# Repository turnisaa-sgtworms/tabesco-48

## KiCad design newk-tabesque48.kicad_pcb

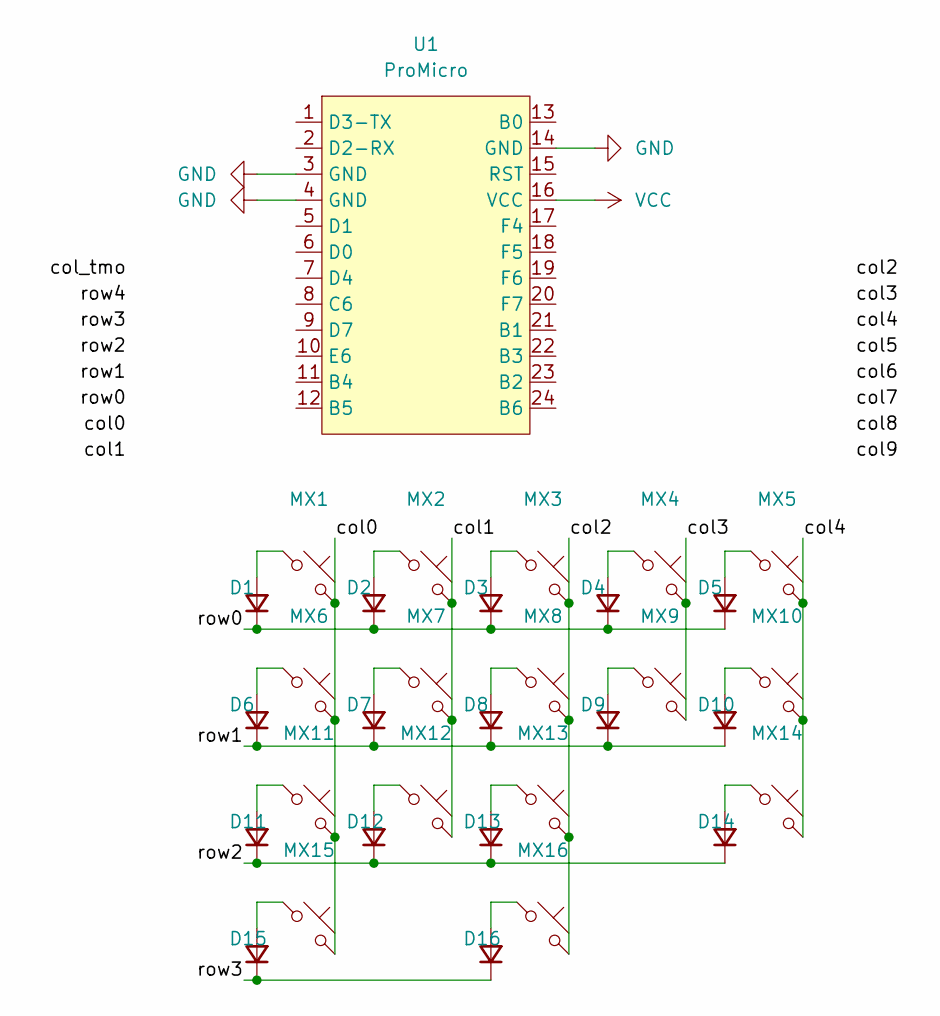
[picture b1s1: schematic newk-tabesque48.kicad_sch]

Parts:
D1, D2, D3, D4, D5, D6, D7, D8, D9, D10, D11, D12, D13, D14, D15, D16: D_Small; D_SOD-123
MX1, MX2, MX3, MX4, MX5, MX6, MX7, MX8, MX9, MX10, MX11, MX12, MX13, MX14, MX15, MX16: MX_SW_HS; SW_MX_HS_CPG151101S11_1u
U1: ProMicro; ProMicro_USBdn

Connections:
/col0: MX1.2, MX6.2, MX11.2, MX15.2
/col1: MX2.2, MX7.2, MX12.2
/col2: MX3.2, MX8.2, MX13.2, MX16.2
/col3: MX4.2, MX9.2
/col4: MX5.2, MX10.2, MX14.2
/row0: D1.1 (K), D2.1 (K), D3.1 (K), D4.1 (K), D5.1 (K)
/row1: D6.1 (K), D7.1 (K), D8.1 (K), D9.1 (K), D10.1 (K)
/row2: D11.1 (K), D12.1 (K), D13.1 (K), D14.1 (K)
/row3: D15.1 (K), D16.1 (K)
GND: U1.3 (GND), U1.4 (GND), U1.14 (GND)
unnamed: D1.2 (A), MX1.1
unnamed: D2.2 (A), MX2.1
unnamed: D3.2 (A), MX3.1
unnamed: D4.2 (A), MX4.1
unnamed: D5.2 (A), MX5.1
unnamed: D6.2 (A), MX6.1
unnamed: D7.2 (A), MX7.1
unnamed: D8.2 (A), MX8.1
unnamed: D9.2 (A), MX9.1
unnamed: D10.2 (A), MX10.1
unnamed: D11.2 (A), MX11.1
unnamed: D12.2 (A), MX12.1
unnamed: D13.2 (A), MX13.1
unnamed: D14.2 (A), MX14.1
unnamed: D15.2 (A), MX15.1
unnamed: D16.2 (A), MX16.1
VCC: U1.16 (VCC)

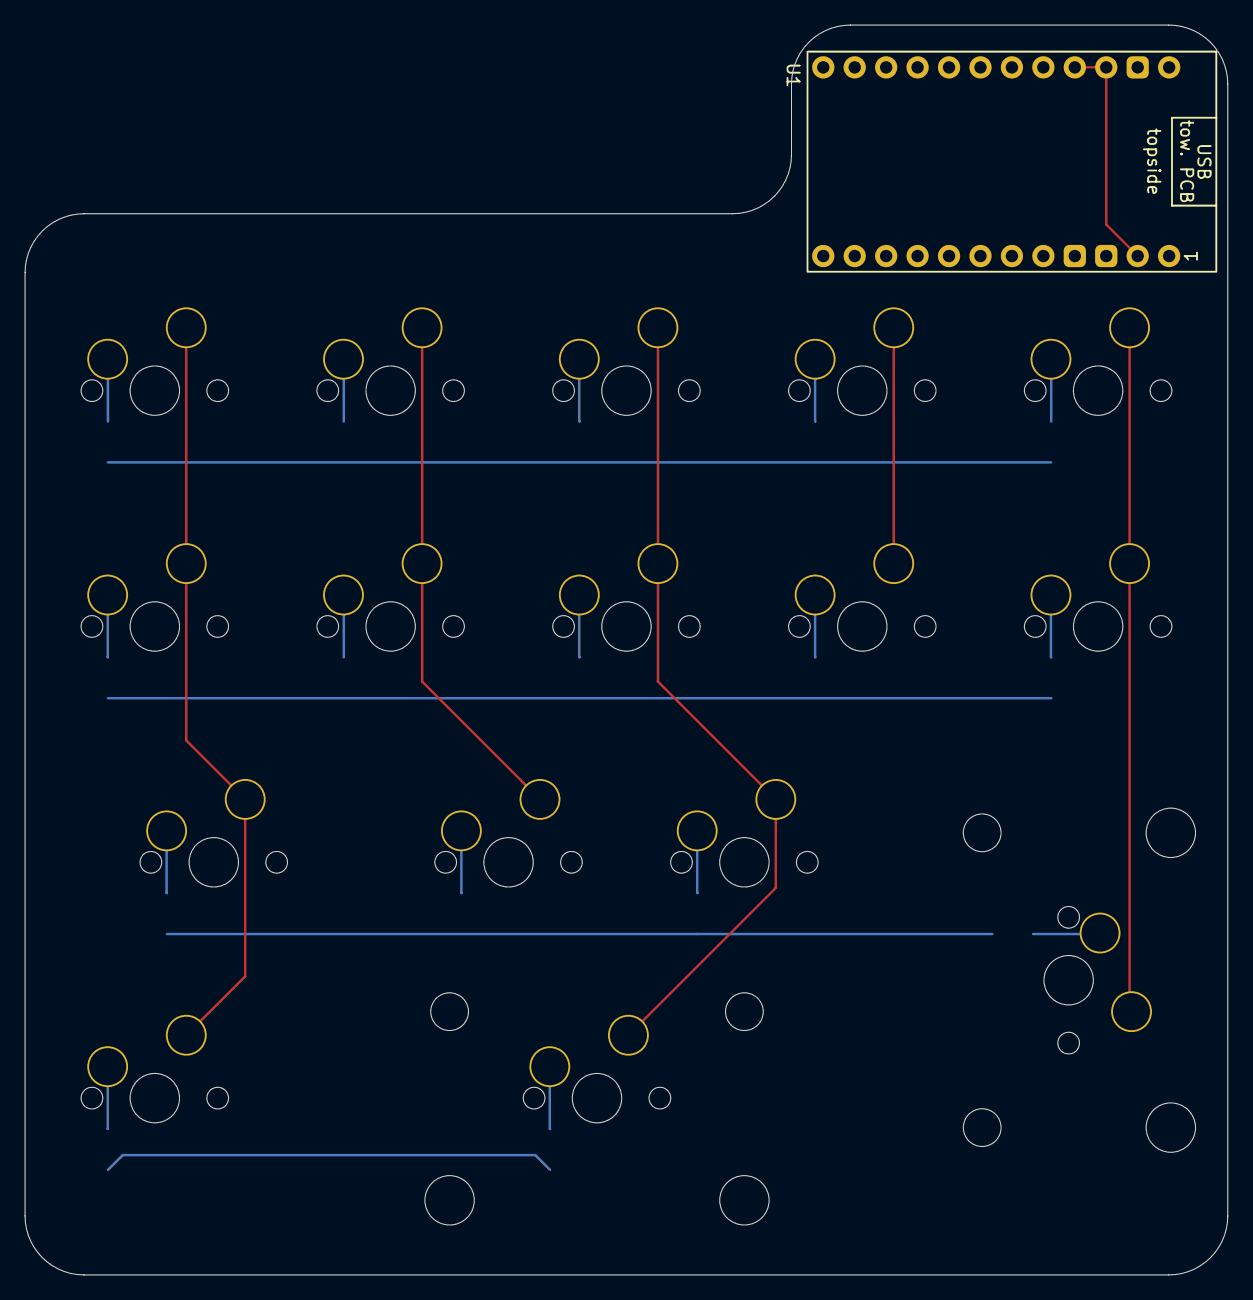
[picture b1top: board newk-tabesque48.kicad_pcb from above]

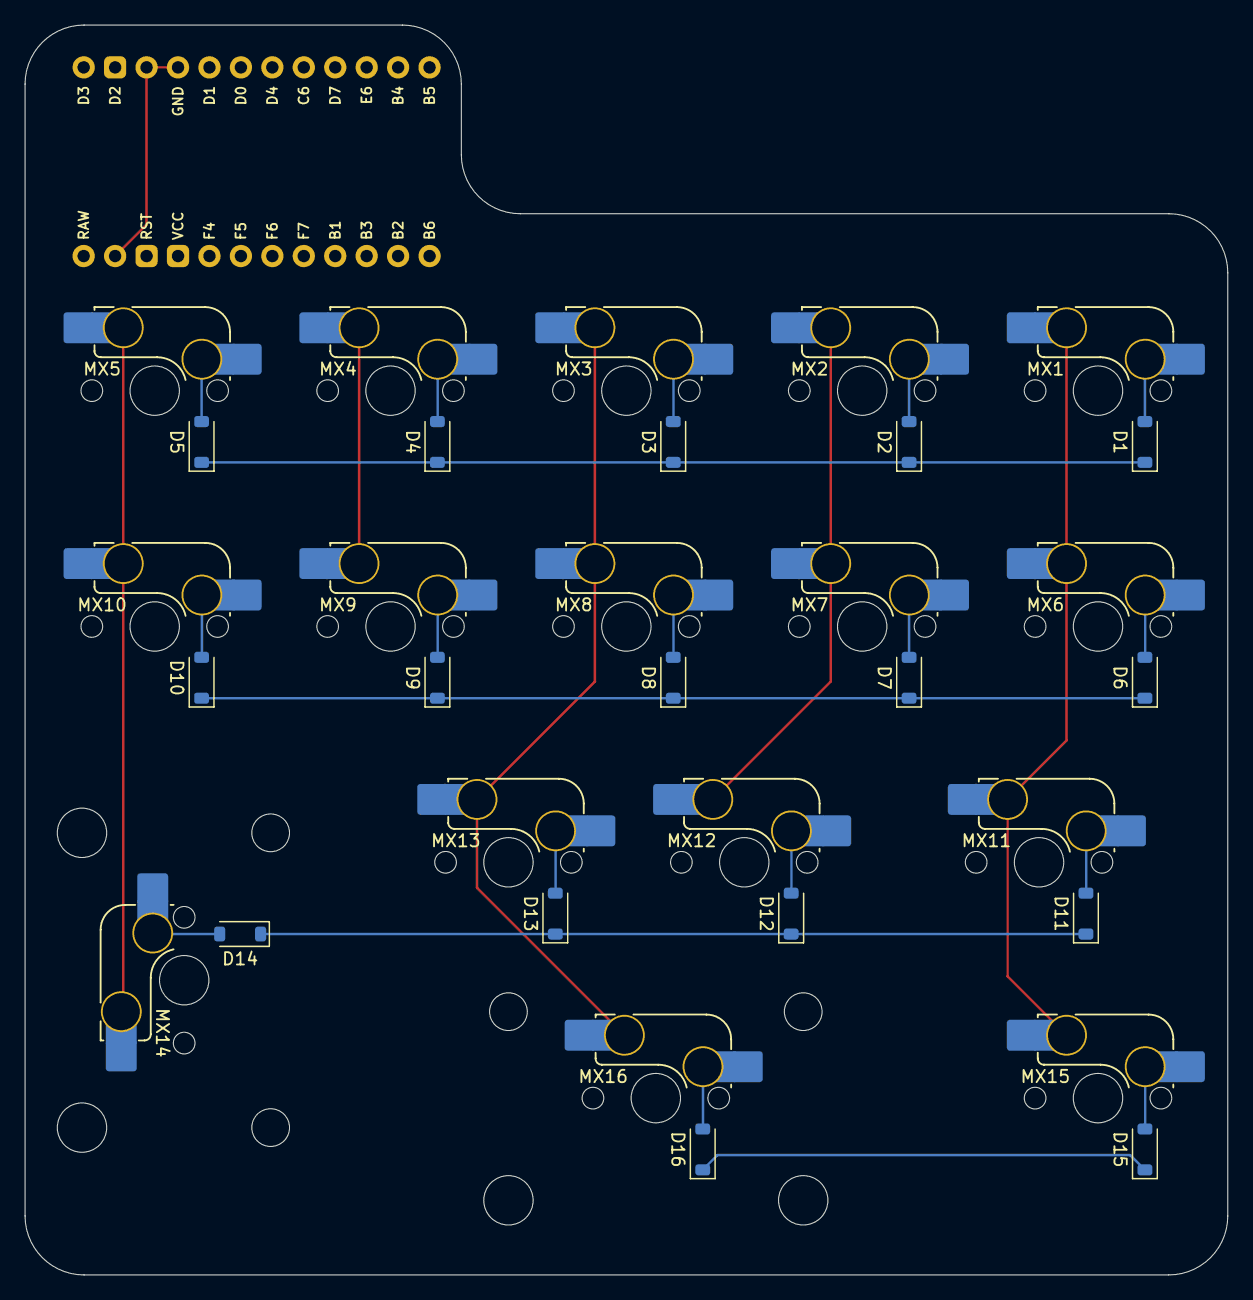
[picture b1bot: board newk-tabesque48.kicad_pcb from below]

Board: 2 copper layers, 97.2 x 101.0 mm, 33 parts (32 on the bottom side), 26 nets.

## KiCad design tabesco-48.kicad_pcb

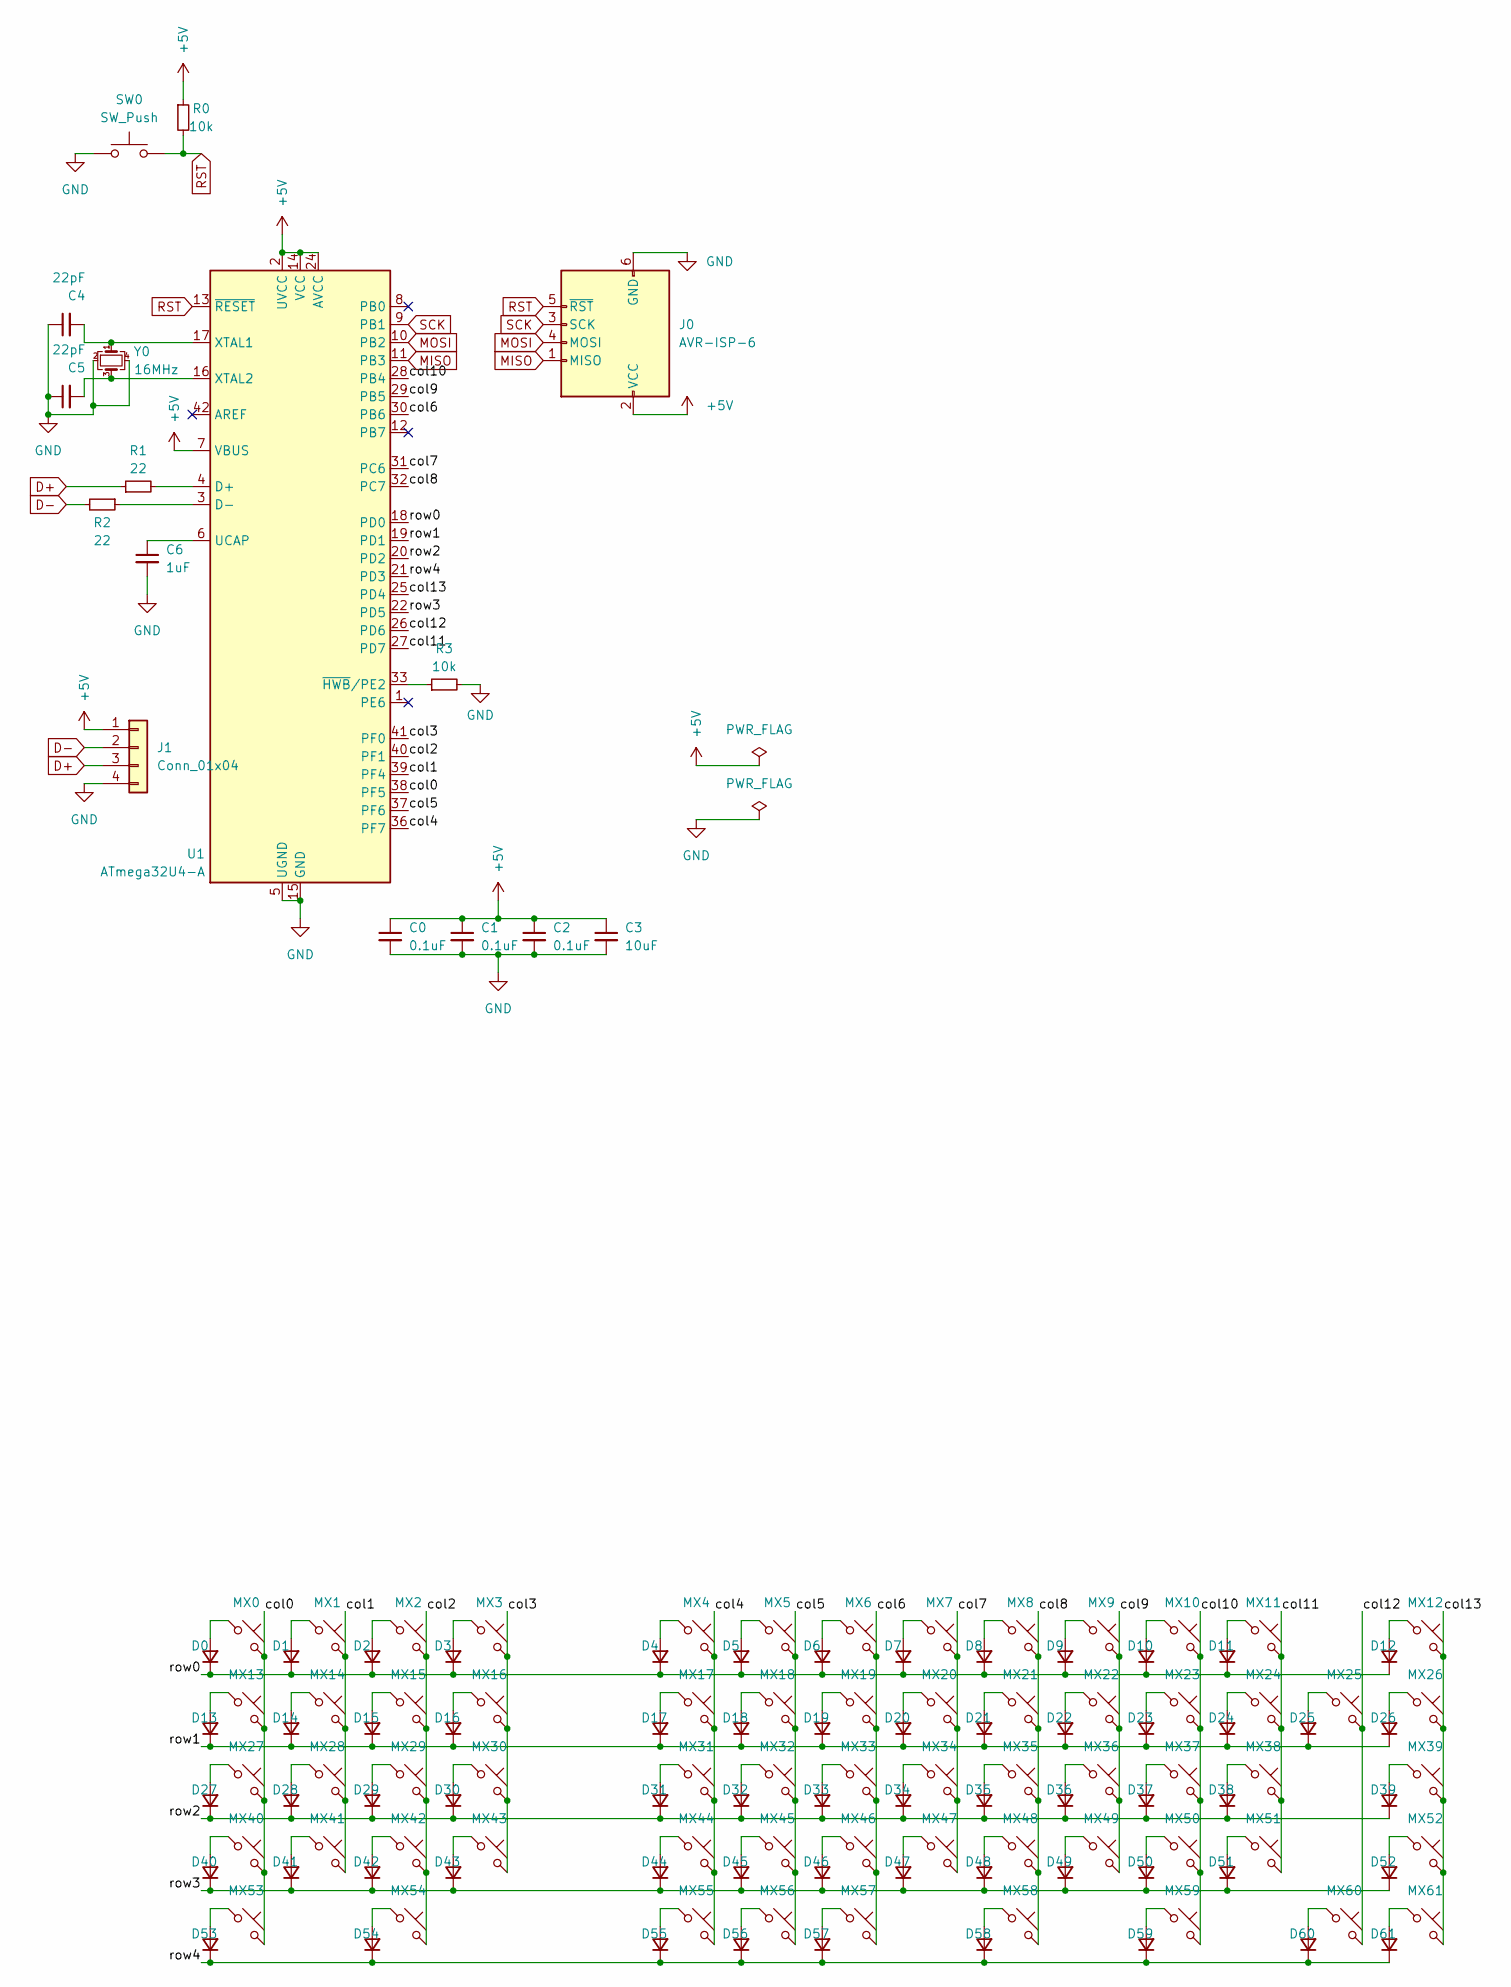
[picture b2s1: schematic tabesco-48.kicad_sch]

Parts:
C0, C1, C2: 0.1uF; C_0805_2012Metric
C3: 10uF; C_0805_2012Metric
C4, C5: 22pF; C_0805_2012Metric
C6: 1uF; C_0805_2012Metric
D0, D1, D2, D3, D4, D5, D6, D7, D8, D9, D10, D11, D12, D13, D14, D15, D16, D17, D18, D19, D20, D21, D22, D23, D24, D25, D26, D27, D28, D29, D30, D31, D32, D33, D34, D35, D36, D37, D38, D39, D40, D41, D42, D43, D44, D45, D46, D47, D48, D49, D50, D51, D52, D53, D54, D55, D56, D57, D58, D59, D60, D61: D_Small; D_SOD-123
J0: AVR-ISP-6; PinHeader_2x03_P1.00mm_Vertical
J1: Conn_01x04; JST_SH_SM04B-SRSS-TB_1x04-1MP_P1.00mm_Horizontal
MX0, MX1, MX2, MX3, MX5, MX6, MX7, MX8, MX9, MX10, MX11, MX13, MX14, MX15, MX16, MX18, MX19, MX20, MX21, MX22, MX23, MX24, MX25, MX27, MX28, MX29, MX30, MX32, MX33, MX34, MX35, MX36, MX37, MX38, MX40, MX41, MX42, MX43, MX45, MX46, MX47, MX48, MX49, MX50, MX51, MX52, MX53, MX54, MX56, MX58, MX59, MX60, MX61: MX_SW_HS; SW_MX_HS_CPG151101S11_1u
MX4, MX12, MX31, MX39: MX_SW_HS; SW_MX_HS_CPG151101S11_1.75u
MX17, MX26, MX55, MX57: MX_SW_HS; SW_MX_HS_CPG151101S11_1.25u
MX44: MX_SW_HS; SW_MX_HS_CPG151101S11_1.5u
R0, R3: 10k; R_0805_2012Metric
R1, R2: 22; R_0805_2012Metric
SW0: SW_Push; SW_Tactile_Straight_KSA0Axx1LFTR
U1: ATmega32U4-A; TQFP-44_10x10mm_P0.8mm
Y0: 16MHz; Crystal_SMD_3225-4Pin_3.2x2.5mm

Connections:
+5V: C0.1, C1.1, C2.1, C3.1, J0.2 (VCC), J1.1, R0.1, U1.2 (UVCC), U1.7 (VBUS), U1.14 (VCC), U1.24 (AVCC), U1.34 (VCC), U1.44 (AVCC)
/col0: MX0.2, MX13.2, MX27.2, MX40.2, MX53.2, U1.38 (PF5)
/col1: MX1.2, MX14.2, MX28.2, MX41.2, U1.39 (PF4)
/col2: MX2.2, MX15.2, MX29.2, MX42.2, MX54.2, U1.40 (PF1)
/col3: MX3.2, MX16.2, MX30.2, MX43.2, U1.41 (PF0)
/col4: MX4.2, MX17.2, MX31.2, MX44.2, MX55.2, U1.36 (PF7)
/col5: MX5.2, MX18.2, MX32.2, MX45.2, MX56.2, U1.37 (PF6)
/col6: MX6.2, MX19.2, MX33.2, MX46.2, MX57.2, U1.30 (PB6)
/col7: MX7.2, MX20.2, MX34.2, MX47.2, U1.31 (PC6)
/col8: MX8.2, MX21.2, MX35.2, MX48.2, MX58.2, U1.32 (PC7)
/col9: MX9.2, MX22.2, MX36.2, MX49.2, U1.29 (PB5)
/col10: MX10.2, MX23.2, MX37.2, MX50.2, MX59.2, U1.28 (PB4)
/col11: MX11.2, MX24.2, MX38.2, MX51.2, U1.27 (PD7)
/col12: MX25.2, MX60.2, U1.26 (PD6)
/col13: MX12.2, MX26.2, MX39.2, MX52.2, MX61.2, U1.25 (PD4)
/row0: D0.1 (K), D1.1 (K), D2.1 (K), D3.1 (K), D4.1 (K), D5.1 (K), D6.1 (K), D7.1 (K), D8.1 (K), D9.1 (K), D10.1 (K), D11.1 (K), D12.1 (K), U1.18 (PD0)
/row1: D13.1 (K), D14.1 (K), D15.1 (K), D16.1 (K), D17.1 (K), D18.1 (K), D19.1 (K), D20.1 (K), D21.1 (K), D22.1 (K), D23.1 (K), D24.1 (K), D25.1 (K), D26.1 (K), U1.19 (PD1)
/row2: D27.1 (K), D28.1 (K), D29.1 (K), D30.1 (K), D31.1 (K), D32.1 (K), D33.1 (K), D34.1 (K), D35.1 (K), D36.1 (K), D37.1 (K), D38.1 (K), D39.1 (K), U1.20 (PD2)
/row3: D40.1 (K), D41.1 (K), D42.1 (K), D43.1 (K), D44.1 (K), D45.1 (K), D46.1 (K), D47.1 (K), D48.1 (K), D49.1 (K), D50.1 (K), D51.1 (K), D52.1 (K), U1.22 (PD5)
/row4: D53.1 (K), D54.1 (K), D55.1 (K), D56.1 (K), D57.1 (K), D58.1 (K), D59.1 (K), D60.1 (K), D61.1 (K), U1.21 (PD3)
D+: J1.3, R1.1
D-: J1.2, R2.2
GND: C0.2, C1.2, C2.2, C3.2, C4.1, C5.1, C6.2, J0.6 (GND), J1.4, R3.2, SW0.1, U1.5 (UGND), U1.15 (GND), U1.23 (GND), U1.35 (GND), U1.43 (GND), Y0.2, Y0.4
MISO: J0.1 (MISO), U1.11 (PB3)
MOSI: J0.4 (MOSI), U1.10 (PB2)
unnamed: D0.2 (A), MX0.1
unnamed: D1.2 (A), MX1.1
unnamed: D2.2 (A), MX2.1
unnamed: D3.2 (A), MX3.1
unnamed: D4.2 (A), MX4.1
unnamed: D5.2 (A), MX5.1
unnamed: D6.2 (A), MX6.1
unnamed: D7.2 (A), MX7.1
unnamed: D8.2 (A), MX8.1
unnamed: D9.2 (A), MX9.1
unnamed: D10.2 (A), MX10.1
unnamed: D11.2 (A), MX11.1
unnamed: D12.2 (A), MX12.1
unnamed: D13.2 (A), MX13.1
unnamed: D14.2 (A), MX14.1
unnamed: D15.2 (A), MX15.1
unnamed: D16.2 (A), MX16.1
unnamed: D17.2 (A), MX17.1
unnamed: D18.2 (A), MX18.1
unnamed: D19.2 (A), MX19.1
unnamed: D20.2 (A), MX20.1
unnamed: D21.2 (A), MX21.1
unnamed: D22.2 (A), MX22.1
unnamed: D23.2 (A), MX23.1
unnamed: D24.2 (A), MX24.1
unnamed: D25.2 (A), MX25.1
unnamed: D26.2 (A), MX26.1
unnamed: D27.2 (A), MX27.1
unnamed: D28.2 (A), MX28.1
unnamed: D29.2 (A), MX29.1
unnamed: D30.2 (A), MX30.1
unnamed: D31.2 (A), MX31.1
unnamed: D32.2 (A), MX32.1
unnamed: D33.2 (A), MX33.1
unnamed: D34.2 (A), MX34.1
unnamed: D35.2 (A), MX35.1
unnamed: D36.2 (A), MX36.1
unnamed: D37.2 (A), MX37.1
unnamed: D38.2 (A), MX38.1
unnamed: D39.2 (A), MX39.1
unnamed: D40.2 (A), MX40.1
unnamed: D41.2 (A), MX41.1
unnamed: D42.2 (A), MX42.1
unnamed: D43.2 (A), MX43.1
unnamed: D44.2 (A), MX44.1
unnamed: D45.2 (A), MX45.1
unnamed: D46.2 (A), MX46.1
unnamed: D47.2 (A), MX47.1
unnamed: D48.2 (A), MX48.1
unnamed: D49.2 (A), MX49.1
unnamed: D50.2 (A), MX50.1
unnamed: D51.2 (A), MX51.1
unnamed: D52.2 (A), MX52.1
unnamed: D53.2 (A), MX53.1
unnamed: D54.2 (A), MX54.1
unnamed: D55.2 (A), MX55.1
unnamed: D56.2 (A), MX56.1
unnamed: D57.2 (A), MX57.1
unnamed: D58.2 (A), MX58.1
unnamed: D59.2 (A), MX59.1
unnamed: D60.2 (A), MX60.1
unnamed: D61.2 (A), MX61.1
unnamed: R1.2, U1.4 (D+)
unnamed: R2.1, U1.3 (D-)
unnamed: C6.1, U1.6 (UCAP)
unnamed: C4.2, U1.17 (XTAL1), Y0.1
unnamed: C5.2, U1.16 (XTAL2), Y0.3
unnamed: R3.1, U1.33 (~HWB/PE2)
RST: J0.5 (~RST), R0.2, SW0.2, U1.13 (~RESET)
SCK: J0.3 (SCK), U1.9 (PB1)

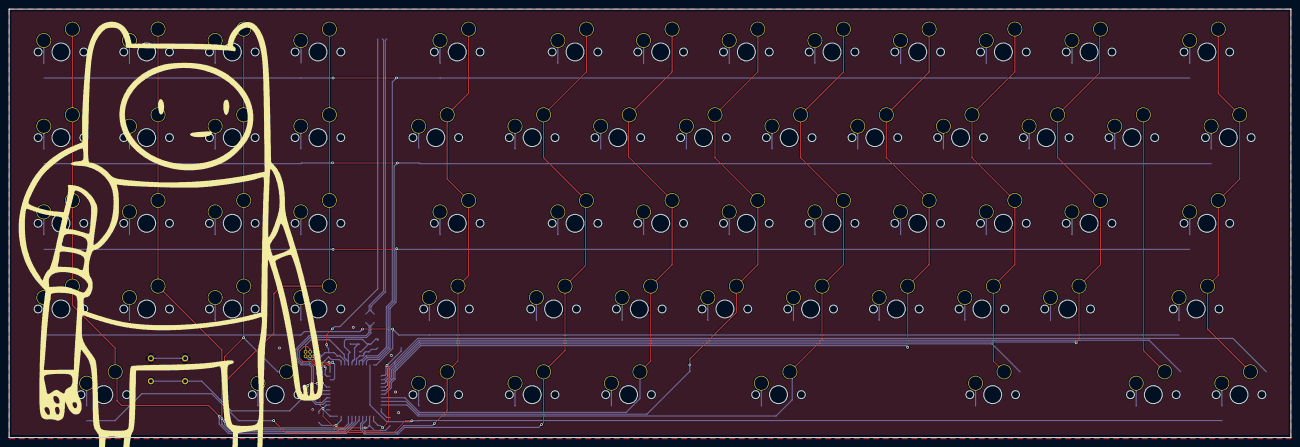
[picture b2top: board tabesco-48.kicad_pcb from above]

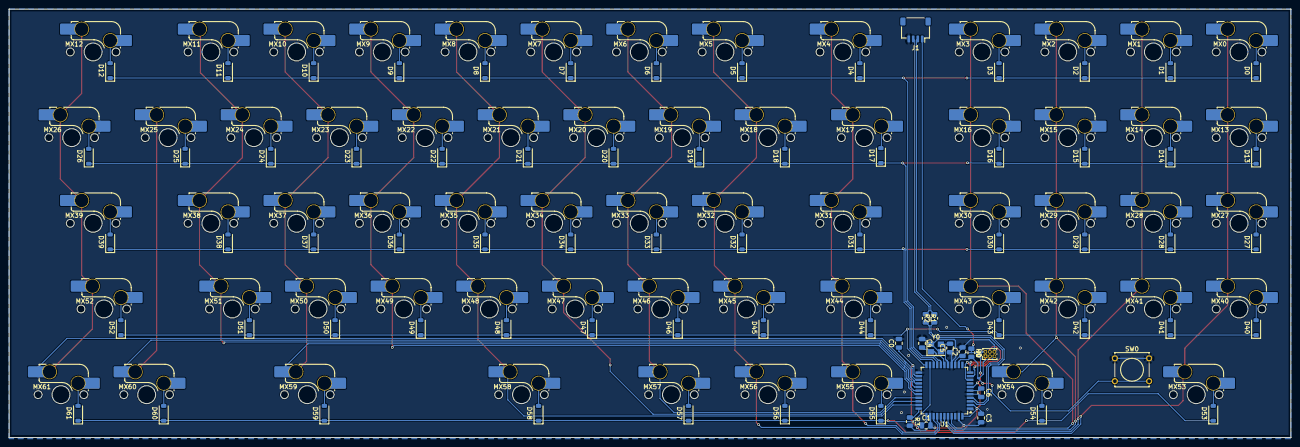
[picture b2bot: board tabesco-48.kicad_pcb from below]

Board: 2 copper layers, 285.0 x 95.2 mm, 140 parts (140 on the bottom side), 95 nets.

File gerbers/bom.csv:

Designator,Footprint,Quantity,Value,LCSC Part #
"D1, D10, D11, D12, D13, D14, D15, D16, D17, D18, D19, D2, D20, D21, D22, D23, D24, D25, D26, D27, D28, D29, D3, D30, D31, D32, D33, D34, D35, D36, D37, D38, D39, D4, D40, D41, D42, D43, D44, D45, D46, D47, D48, D5, D6, D7, D8, D9",D_SOD-123,48,D_Small,C81598
"MX1, MX10, MX11, MX12, MX13, MX14, MX15, MX16, MX17, MX18, MX19, MX2, MX20, MX21, MX22, MX23, MX24, MX25, MX26, MX27, MX28, MX29, MX3, MX30, MX31, MX32, MX33, MX34, MX35, MX36, MX37, MX38, MX39, MX4, MX40, MX41, MX42, MX43, MX44, MX45, MX46, MX47, MX48, MX5, MX6, MX7, MX8, MX9",SW_MX_HS_CPG151101S11_1u,48,MX_SW_HS,C41430893
SW1,SW_Tactile_Straight_KSA0Axx1LFTR,1,SW_Push,

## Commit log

2024-11-21 created sch and pcb
2024-11-21 created gerber
2024-11-21 work and stuff i don't remember lots of fusion
2024-11-22 buncha stuff again
2024-11-28 created tabasco slide verson
2024-12-02 renamed repo and files
2024-12-02 created 6 key tapdance pad 2007 rot brains stupid
2024-12-04 final draft (?)
2024-12-12 created tabesco-31
2024-12-12 work on 31
2024-12-12 tabesco31 pcb done(?)
2024-12-12 more work, transitioning to IC in seperate repo
2024-12-12 brain mode
2024-12-13 finished tabesco-34
2024-12-13 swagbord case
2024-12-14 fixed issue with usb C port placement
2024-12-19 created tabesco-60
2024-12-20 finished(?) tabesco-60
2024-12-20 prepping for kicanvas
2024-12-20 more prep 4 kicanvas
2024-12-20 fixed(?) UDB connector, some GND fill work
2024-12-20 sch/pcb adjustments (UDB)
2024-12-20 BOM/CPL generated
2024-12-23 reorganized idk
2025-04-10 added case files
2025-04-10 added firmware and pcb ordering stuff
2025-05-23 skinny case moment
    HUGE news!
    tabesco lost some weight!
    now with a microscopic 21mm frontheight!!! wow!
